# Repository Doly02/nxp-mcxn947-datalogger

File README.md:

## Digital Data Logger with Information Loss Prevention in Case of Power Failure

- Author: Tomáš Dolák 
- Login: [xdolak09](https://www.vut.cz/lide/tomas-dolak-247220)
- Email: <xdolak09@stud.fit.vutbr.cz>
- Supervisor: Ing. Václav Šímek
- Consultant: Ing. Martin Moštěk PhD. (NXP Semiconductors)

The goal of this project is to develop a digital data logger that captures serial data from a UART peripheral, timestamps it, and stores the logged data on an SD card.
A key requirement of the implementation is to ensure data integrity by preventing loss in the event of a power failure. This digital data logger was developed based on the requirements provided by the Wireless Charging Team at NXP Semiconductors.

### Table of Contents
- [Requirements](#requirements)
  - [Hardware Components](#hardware-components)
  - [Software Requirements](#software-requirements)
- [Repository Organization](#repository-organization)
- [How to Use the Digital Data Logger](#how-to-use-the-digital-data-logger)
  - [USB Interfaces](#usb-interfaces)
  - [Signal Diodes](#signal-diodes)
  - [Data Recording](#data-recording)
  - [Reading Data from the Data Logger](#reading-data-from-the-data-logger)
  - [Structure of Logged Data](#structure-of-logged-data)
  - [Format of Logged Entries](#format-of-logged-entries)
- [Developer Notes](#developer-notes)
  - [Modules](#modules)
- [Testing](#testing)
  - [Functional Testing](#functional-testing)
  - [Static Code Analysis](#static-code-analysis)
- [Documentation](#documentation)
- [Known Issues](#known-issues)
- [References](#references)

### Requirements 
To build and run `datalogger`, you will need the following:

#### Hardware Components
1. NXP FRDM-MCXN947 Development Board
2. Expansion Shield Proposed in This Bachelor Thesis

#### Software Requirements
1. MCUXpresso IDE v11.10.0 With GCC-based ARM Embedded Toolchain (Arm-none-eabi-gcc Compiler)
1. NXP SDK FRDM-MCXN947 Version 2.16.000

### Repository Organization
```
/nxp-mcxn947-datalogger
├── application/                 # Main Directory With Digital Recorder Firmware.
│   ├── src/                  # Contains The Firmware Source Files.
│   ├── doc/                     # HTML and LaTeX Firmware Documentation Generated by Doxygen.
│   ├── include/                 # Contains The Firmware Header Files.
│   └── others...                # Project Files (.cproject & .project), Libraries (e.g. FATFS), FreeRTOS, Utilities, Modules and Drivers From NXP SDK.
│
├── hardware/
│   ├── components/              # List of Used Hardware Components on Expansion Shield.
│   ├── design/                  # KiCAD Project Containing Schematic and PCB Design.
│   └── pinout_datalogger.xlsx   # Table With Overview of Microcontroller Pin Connections.
├── power_consumption/           # Digital Data Logger Power Consumption Data, Measured By Power Profiler Kit II. [1]
├── tests/
│   ├── functional_tests/        # Functional Test Folder For Verifying Correct Data Collection.
│   │   ├── test_files/          # Test Files Used By serial_tests.py Script.
│   │   ├── stress_test.py       # Script With Stress Test For Digital Data Logger Sends Data Continiously With Baudrate 921600.
│   │   └── serial_tests.py      # serial_tests.py Script.
│   └── static_analysis/
│       ├── outputs/             # Contains Outputs of Static Code Analysis According To MISRA C:2012 Rules, Performed by PC-lint Tool.
│       ├── parsers/             # Contains Parsers That Filter Rule-Breakings MISRA Rules From The Required and Mandatory Categories.
│       ├── lint_config.lnt      # Configuration File of PC Lint Plus.
│       └── sources.lst          # Defines a Set of Files To Be Analyzed by PC Lint Plus.
│
├── thesis/                                     # Sub-Module
│   ├── xdolak09-bthesis.tex                    # Main LaTeX Project of Technical Report.
│   ├── project-01-kapitoly-chapters.tex        # Chapters LaTeX Project of Technical Report.
│   ├── project-20-literatura-bibliography.bib  # Bibliography of Technical Report.
│   ├── project-30-prilohy-appendices.tex       # Appendices of Technical Report.
│   ├── table-of-extraneous-words.tex           # Table of Extraneous Words in Technical Report.
│   ├── bib-styles
│   ├── obrazky-figures/         # Used Figures.
│   ├── template-fig/            # VUT Logo.
│   └── diagrams/                # Created Digrams For Technical Report.
│
├── config                       # Contains a Sample Configuration File That Can Be Used To Configure The Behaviour of The Digital Recorder.
├── README.md
```

### How to Use the Digital Data Logger

#### Signal Diodes

The digital data logger is equipped with five status LEDs (labeled 1–5) located on the front side of the enclosure. These LEDs visually indicate the current operational state of the logger.

The image below shows the placement and labeling of each LED on the front panel of the enclosure:

<p align="center">
  <br>
  <em>Data logger status LEDs </em><br>
</p>

The table below describes the function of each LED:

| LED | Description |
|-----|-------------|
| 1   | Lights up when the available free space on the SD card falls below the limit defined by the `free_space` parameter in the configuration file. |
| 2   | Indicates an error condition. This LED turns on if the configuration file is invalid or if a critical error occurs during data recording (e.g., file creation failure or UART framing error). |
| 3   | Signals that the data logger is no longer actively recording. This state occurs, for example, when the monitored device stops transmitting data or is disconnected. |
| 4   | Blinks during active data recording to indicate that data is being received and saved to the SD card. |
| 5   | Lights up approximately 16 seconds after powering the logger to indicate that the backup capacitor is sufficiently charged. Once lit, it is safe to disconnect the device from power without risking data loss. |

#### Data Recording
1. **(Optional But Recommended)** Prepare the configuration file `config`, which should be placed in the root directory of the SD card.  
This file allows you to customize the data logger's behavior instead of using the default configuration.

<p align="center">
  <br>
  <em>Location of the config file on the SD card</em><br>
</p>

Example content of `config`:
```
baudrate=115200
file_size=2048
stop_bits=1
data_bits=8
parity=none
free_space=50
```
- **Note:** The order of parameters is not fixed.

If some of the parameters in the configuration file are missing or the configuration file is missing completely,  
the default values defined in the `defs.h` file are used.

| Parameter      | Default Value                 | Data Type                      |
|----------------|-------------------------------|--------------------------------|
| `baudrate`     | `230400`                      | uint32_t                       |
| `file_size`    | `8192`                        | uint32_t (in KiB)              |
| `stop_bits`    | `kLPUART_OneStopBit`          | enum (lpuart_stop_bit_count_t) |
| `data_bits`    | `kLPUART_EightDataBits`       | enum (lpuart_data_bits_t)      |
| `parity`       | `kLPUART_ParityDisabled`      | enum (lpuart_parity_mode_t)    |
| `free_space`   | `50`                          | uint32_t (in MiB)              |

2. Insert the SD card (type SDHC) into the data logger.

3. Power on the data logger via USB or another power source. The data logger will automatically:
- Load the configuration from `config` (if present)
- After startup, the data logger enters the recording mode by default. At the beginning of the record task, it initializes the SD card, and if a new or unformatted card is detected,  
  the firmware will automatically format it and initialize the FAT file system with 32-bit LBA.

4. Wait until the LED 5 indicator turns on.  
   This LED indicates that the digital data logger can be safely disconnected without the risk of data loss or file system corruption.

5. Connect the digital data logger to the monitored device that transmits serial data via UART.  
   Once the data transmission starts, the data logger will indicate active reception by blinking a dedicated LED 4,  
   which is shown in the following image.

6. At this point, the digital data logger is actively recording incoming UART data.  
   During recording, the same LED continuously blinks to indicate that data logging is in progress.

7. If an error occurs during UART data reception (e.g. framing error),  
   the digital data logger will illuminate a separate error LED 2  
   to indicate that logging has been interrupted due to a fault.

   If the error prevents further data reception, an additional LED 3 will also light up  
   to signal that the device can no longer continue logging until it is restarted or the error is resolved.

8. To safely stop data logging, disconnect the digital data logger from the monitored device.  
   At this point, all buffered data will be properly finalized and stored on the SD card.  
   The status LED D3 will then light up to indicate that data reception has been halted  
   and the device is in standby mode.

9. To resume data logging after it has been halted, simply reconnect the digital data logger  
   to the monitored UART device. The logger will automatically return to recording mode  
   (described in step 6) and continue capturing incoming data.

10. In the event of a power disconnection during logging,  
    the digital data logger detects the power loss and automatically saves all buffered data.  
    The recording is then gracefully finalized to prevent data loss or file system corruption.

#### Reading Data from the Data Logger
To read the recorded data from the digital data logger, simply connect the device to a computer using the USB1_HS connector.  
The data logger will automatically switch into data access mode (MSC mode), and the SD card will be exposed as a standard mass storage device,  
allowing the user to copy the recorded data files.

<p align="center">
  <br>
  <em>Organization of session directories with logs on SD cards</em><br>
</p>

#### Structure of Logged Data
After each startup, the data logger creates a new session directory in which all the logs from the current runtime are stored.  
These session folders are organized by the date and an incrementing counter in the format:

```
YYYYMMDD_X/
```

Where:  
- `YYYYMMDD` is the date of the session creation  
- `X` is an integer session index used to differentiate multiple sessions created on the same day

After data has been recorded, each session folder contains text-based log files storing the data collected during the corresponding session.  
The maximum size of each log file is determined by the `file_size` parameter defined in the configuration file (see chapter on configuration).  
Log files are named using the following format:

```
YYYYMMDD_HHMMSS_X.txt
```

- `YYYYMMDD_HHMMSS` is the timestamp when the log file was created  
- `X` is an index used to differentiate multiple files created at the same second

#### Format of Logged Entries
Each logged line represents a single data record terminated by a line break sequence (`\r\n`).  
Every line is prefixed with a timestamp in the format:

```
(HH:MM:SS) Logged Message
```

This timestamp represents the time when the specific data was captured by the logger.  
The following example illustrates the typical appearance of consecutive logged lines in a file:

```
(00:10:16) New Data 23741
(00:10:16) New Data 23742
(00:10:16) New Data 23743
(00:10:16) New Data 23744
(00:10:16) New Data 23745
(00:10:16) New Data 23746
(00:10:16) New Data 23747
(00:10:16) New Data 23748
(00:10:16) New Data 23749
```

### Developer Notes
All application-level source and header files are located in the `source/` and `include/` directories.

The firmware is structured into several functional modules, such as recording logic, mass storage access, power loss detection, and system status signaling.  
Many of these modules can be individually enabled or disabled as needed. This behavior is achieved through conditional compilation in ISO C, and logic blocks are active only  
if enabled via preprocessor macros. These settings are centrally managed in the application configuration header file `defs.h`.

The `defs.h` configuration file also includes the option to control the verbosity of firmware output messages. The firmware supports three message output levels:

- **Error Messages** (prefixed with `ERR:`) report critical conditions. This level is always active and can't be disabled.

```
PRINTF("ERR: Failed to Create File %s. Error=%d\r\n", u8FileName, (uint32_t)status);
```

- **Informational Messages** (prefixed with `INFO:`) provide context such as initialization progress, configuration file loading, creation of log, etc.

```
PRINTF("INFO: Created Log %s.\r\n", u8FileName);
```

- **Debug messages** (prefixed with `DEBUG:`) offer the most detailed output and include additional technical details useful during development.

```
PRINTF("DEBUG: File System Not Found. Creating FAT File System...\r\n");
```

All of these outputs are provided through the UART serial interface. The firmware uses the `LP_FLEXCOMM4` UART peripheral instance,  
configured with the following parameters:

| Parameter      | Value    | 
|----------------|----------|
| Baudrate       | 115200   |
| Data Bits      | 8        |
| Stop Bit       | 1        |
| Parity         | None     |

The firmware runs on the FreeRTOS real-time operating system. To ensure maximum reliability and predictability, only static memory  
allocation is used throughout the firmware. All tasks and synchronization primitives are created with predefined memory sizes,  
and dynamic memory allocation is fully disabled in the FreeRTOS configuration. Additionally, specific memory allocation functions  
for system tasks such as the idle task and timer task have been implemented to support fully static operation.

The overall hardware and software initialization procedures are handled by the `APP_InitBoard()` function, declared in the header file _app_initialization.h_  
and defined in the source file _app_initialization.c_.

The application consists of two FreeRTOS tasks – _record_task_, which is responsible for recording UART data, and _msc_task_, responsible for exposing the recorded data  
via USB. These tasks are implemented in `app_tasks.c` and `pp_tasks.h`, and are created and started from within the `main.c` file.

### Modules
The application files (`main.c`, `app_tasks.c`, and `app_initialization.c`) utilize the following separate modules.  
Each module has its own source and header file:

- `error` – Handles errors and defines error codes.  
- `led` – Manages LED Indicators For System Status.
- `mass_storage` – Provides access to log files over USB MSC.  
- `parser` – Parses the configuration file (`config`) from the SD card.
- `pwrloss_det` – Detects and reacts to power loss.
- `record` – Implements logic for recording incoming serial data from UART.
- `task_switching` – Includes the method for detection of attached or detached application USB.
- `time` – Provides date/time handling for file naming and timestamping (external and internal RTCs).
- `uart` – Includes initialization (+ configuration), enabling and disabling of the UART peripheral.  
- `temperature` – Extension for temperature measurement using the P3T1755 on-board temperature sensor on the FRDM-MCXN947.

### Testing

#### Functional Testing
The digital data logger was tested using a Python script located in the `tests/` directory under the name `serial_test.py`.

The script `serial_test.py` simulates the monitored device by reading test text files and sending their contents as serial data through the COM port to the digital data logger.  
There is a time delay between each file being sent, which deliberately causes the `CONSOLELOG_Flush()` function to be called,  
so that each test input is recorded in a separate file that can be compared against the original test file.

Scripted testing was performed at various baud rates, with testing primarily focused on baud rates corresponding to actual deployment scenarios.  
After the test was completed, the recorded outputs were compared to the original test files. The results of the comparison confirmed that in all cases tested,  
the transfer was correct and there was no data loss or corruption.

The digital data logger was also successfully verified using the `stress_test.py` script that contains a stress test.  
In this test, data was sent at 921600 baud. The data was first collected into a circular buffer of 4 KiB,  
from which it was then stored on the SD card in blocks of 4 KiB. The resulting recording files were 1 MiB in size.

Functional testing also covered the behavior of the digital recorder in non-standard scenarios that may occur during real-world deployment.The Results are Summarized in Table Below.

| Test description                                                      | Expected result                                                                                   | Passed |
|-----------------------------------------------------------------------|---------------------------------------------------------------------------------------------------|--------|
| Missing configuration file                                            | Error indication using LED D2, recording interrupted                                              | Yes    |
| Missing `baudrate` value in configuration                             | Start recording with default `baudrate` value                                                     | Yes    |
| Recording on a new unformatted SD card                                | SD card is formatted, file system initialized, and device then records incoming data              | Yes    |
| Recording with file size of 512 B                                     | File created and properly closed upon reaching limit                                              | Yes    |
| Recording with file size of 1 MB                                      | File created and properly closed upon reaching limit                                              | Yes    |
| Low free SD card capacity (i.e., below value of parameter `free_space`) | Indication via LED                                                                                | Yes    |
| Transfer of recorded data from the digital recorder                   | Records transferred to host device from the digital recorder                                      | Yes    |

#### Static Code Analysis
In addition to functional testing, static analysis of the source code was performed using rules from the MISRA (_Motor Industry Software Reliability Association_) specification, specifically MISRA C:2012. The focus was primarily on rules classified as required and mandatory. All detected violations in these categories were either corrected or justified through comments in the source code, including a reference to the relevant rule and a rationale for the exception.

The code analysis was performed with tool PC-lint Plus v2.2 developed by Vector. [2]

#### Documentation

This project provides a full range of documentation.

- The hardware and software design concepts are described in detail in the technical report, which is available in folder `thesis/` under name `xdolak09-bthesis.pdf`
- The firmware documentation is located in the `application/doc/` directory. It is generated using Doxygen and available in two formats:
  1. **HTML documentation** - open the file `annotated.html` on the path `application/doc/html/`to start browsing.
  2. **LaTeX documentation** - found under `application/doc/latex` , where the main output file is `refman.pdf`.

### Known Issues
No issues were observed during development, testing, or practical usage of the digital data logger.

### References
[1] "Nordic Semiconductors Power Profiler Kit II" [online]. [cited 2025-5-6]. Available at [https://www.nordicsemi.com/Products/Development-hardware/Power-Profiler-Kit-2](https://www.nordicsemi.com/Products/Development-hardware/Power-Profiler-Kit-2)

[2] "PC-lint Plus 2.2 Static Code Analysis Tool for C and C++ Source Code" [online]. [cited 2025-5-6]. Available at [https://pclintplus.com/](https://pclintplus.com/)

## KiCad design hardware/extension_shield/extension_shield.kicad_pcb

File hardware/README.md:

# Hardware Documentation

This folder contains all hardware-related materials for the expansion shield designed for the FRDM-MCXN947 development board used in data logger project.

### Folder Structure

- `expansion_shield/` – Contains the full KiCad 8 project of the expansion board. This includes the schematic, PCB layout, and associated design files.
- `BOM.csv` – A standard bill of materials generated from KiCad 8 listing the components used on the expansion board.  
- `component.txt` – A human-readable version of the BOM, listing key components along with direct links to online distributors for easy purchasing.  
  **Note:** This list does **not** include passive components such as resistors and capacitor (100 nF) used for the RTC DS3231M+.
- `schematic.pdf` – A PDF version of the complete schematic diagram of the expansion shield for quick reference without needing KiCad.

### Notes
- The KiCad project is created with **KiCad 8**. Make sure to use the correct version to avoid compatibility issues.
- The provided component links in `component.txt` were valid at the time of writing but may change over time depending on distributor availability.

For more information about the system design, refer to the `thesis/` folder or see the main `README` in root folder.

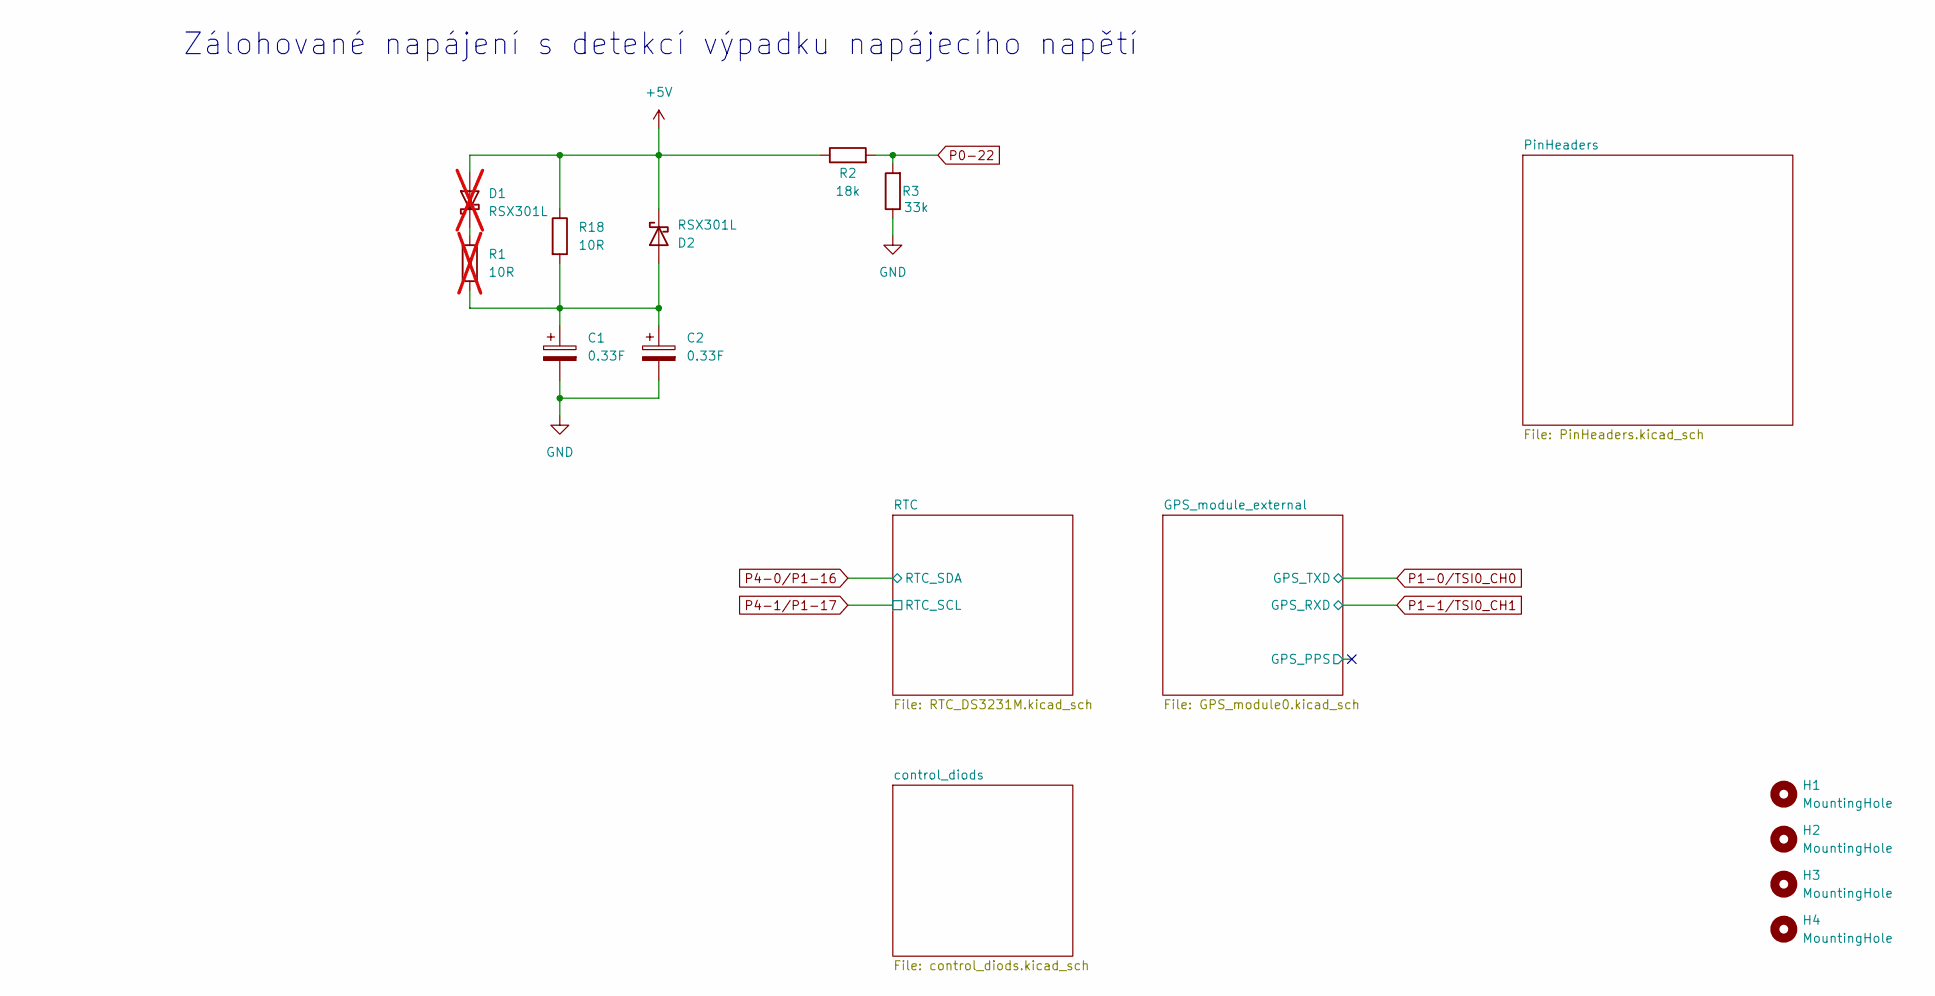
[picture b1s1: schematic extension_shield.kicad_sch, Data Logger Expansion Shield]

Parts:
C1, C2: 0.33F; C_Radial_D8mm_W24mm_L14mm_P13.5mm
D1: RSX301L; D_SMA; not fitted
D2: RSX301L; D_SMA
H1, H2, H3, H4: MountingHole; MountingHole_3.2mm_M3
R1: 10R; R_Axial_DIN0204_L3.6mm_D1.6mm_P5.08mm_Horizontal; not fitted
R2: 18k; R_1206_3216Metric_Pad1.30x1.75mm_HandSolder
R3: 33k; R_1206_3216Metric_Pad1.30x1.75mm_HandSolder
R18: 10R; R_Axial_DIN0204_L3.6mm_D1.6mm_P5.08mm_Horizontal

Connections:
+5V: D1.2 (A), D2.1 (K), R2.1, R18.1; also elsewhere on the board
GND: C1.2, C2.2, R3.1; also elsewhere on the board
unnamed: D1.1 (K), R1.1
unnamed: C1.1, C2.1, D2.2 (A), R1.2, R18.2
P0-22: R2.2, R3.2; also elsewhere on the board

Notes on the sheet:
Zálohované napájení s detekcí výpadku napájecího napětí

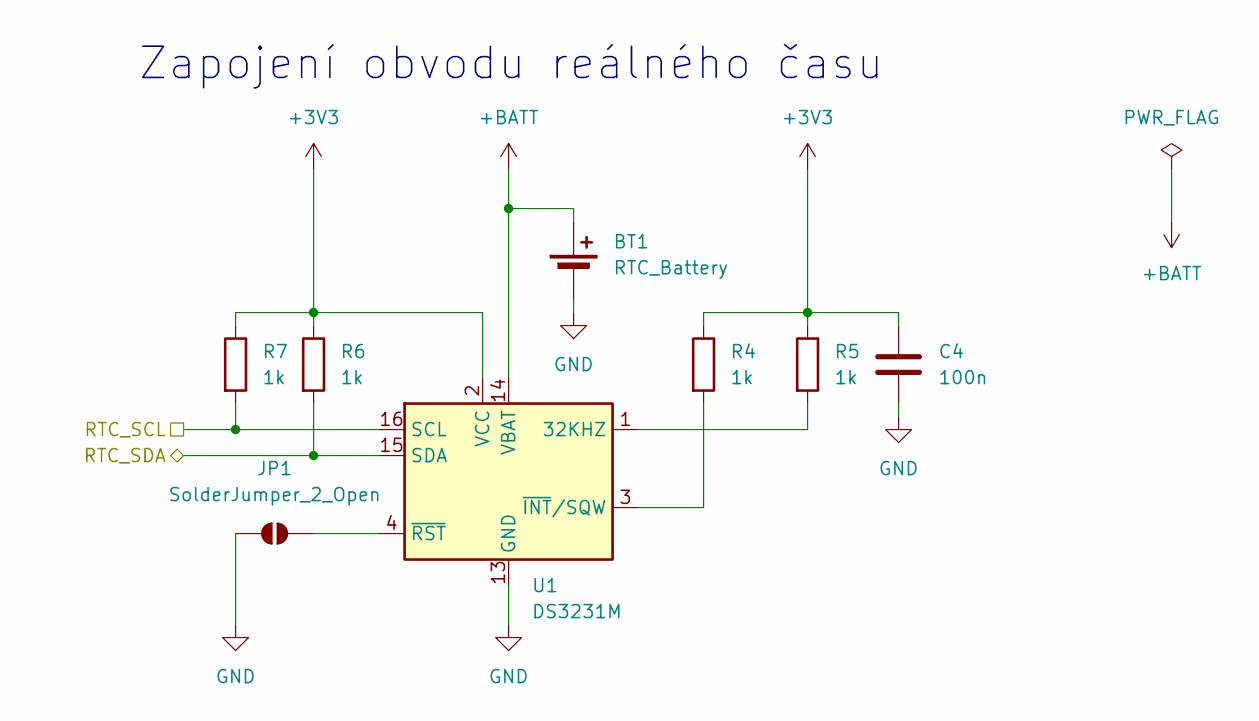
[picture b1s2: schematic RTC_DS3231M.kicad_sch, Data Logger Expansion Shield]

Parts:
BT1: RTC_Battery; Battery_Panasonic_CR2032-HFN_Horizontal_CircularHoles
C4: 100n; C_1206_3216Metric_Pad1.33x1.80mm_HandSolder
JP1: SolderJumper_2_Open; SolderJumper-2_P1.3mm_Open_Pad1.0x1.5mm
R4, R5, R6, R7: 1k; R_1206_3216Metric_Pad1.30x1.75mm_HandSolder
U1: DS3231M; SOIC-16W_7.5x10.3mm_P1.27mm

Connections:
+3V3: C4.1, R4.1, R5.1, R6.1, R7.1, U1.2 (VCC); also elsewhere on the board
+BATT: BT1.1 (+), U1.14 (VBAT)
GND: BT1.2 (-), C4.2, JP1.1 (A), U1.5 (GND), U1.6 (GND), U1.7 (GND), U1.8 (GND), U1.9 (GND), U1.10 (GND), U1.11 (GND), U1.12 (GND), U1.13 (GND); also elsewhere on the board
unnamed: JP1.2 (B), U1.4 (~RST)
unnamed: R5.2, U1.1 (32KHZ)
unnamed: R4.2, U1.3 (~INT/SQW)
P4-0/P1-16: R6.2, U1.15 (SDA); also elsewhere on the board
P4-1/P1-17: R7.2, U1.16 (SCL); also elsewhere on the board

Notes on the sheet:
Zapojení obvodu reálného času

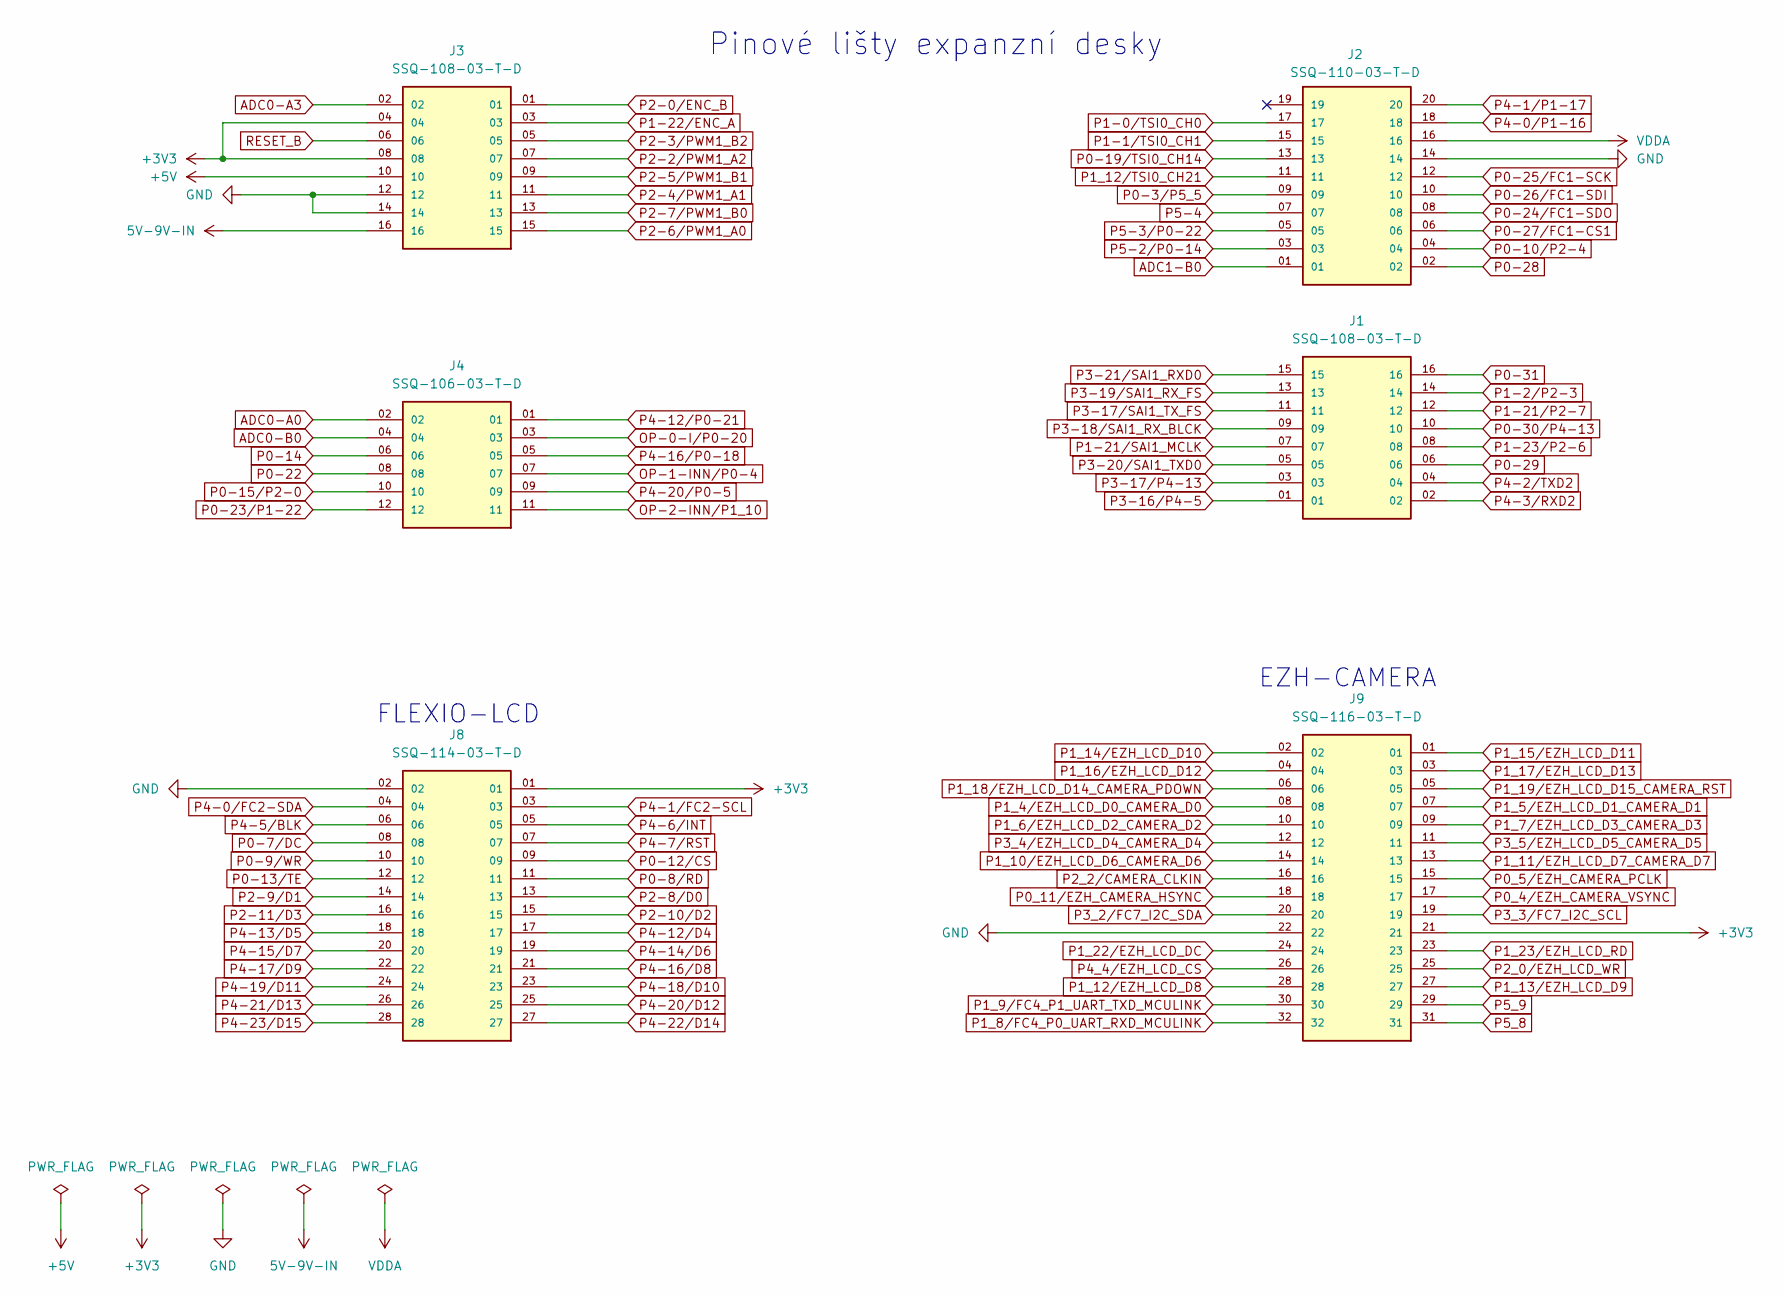
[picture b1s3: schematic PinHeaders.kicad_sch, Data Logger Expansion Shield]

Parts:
J1, J3: SSQ-108-03-T-D; SAMTEC_SSQ-108-XX-X-D; PARTREV A
J2: SSQ-110-03-T-D; SAMTEC_SSQ-110-03-T-D; PARTREV R
J4: SSQ-106-03-T-D; SAMTEC_SSQ-106-03-T-D; PARTREV R
J8: SSQ-114-03-T-D; SAMTEC_SSQ-114-03-T-D; PARTREV R
J9: SSQ-116-03-T-D; SAMTEC_SSQ-116-XX-X-D; PARTREV A

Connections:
5V-9V-IN: J3.16
+3V3: J3.04, J3.08, J8.01, J9.21; also elsewhere on the board
+5V: J3.10; also elsewhere on the board
ADC0-A0: J4.02
ADC0-A3: J3.02
ADC0-B0: J4.04
ADC1-B0: J2.01
GND: J2.14, J3.12, J3.14, J8.02, J9.22; also elsewhere on the board
OP-0-I/P0-20: J4.03
OP-1-INN/P0-4: J4.07
OP-2-INN/P1_10: J4.11
P0-3/P5_5: J2.09
P0-7/DC: J8.08; also elsewhere on the board
P0-8/RD: J8.11
P0-9/WR: J8.10; also elsewhere on the board
P0-10/P2-4: J2.04
P0-12/CS: J8.09
P0-13/TE: J8.12; also elsewhere on the board
P0-14: J4.06
P0-15/P2-0: J4.10
P0-19/TSI0_CH14: J2.13
P0-22: J4.08; also elsewhere on the board
P0-23/P1-22: J4.12
P0-24/FC1-SDO: J2.08
P0-25/FC1-SCK: J2.12
P0-26/FC1-SDI: J2.10
P0-27/FC1-CS1: J2.06
P0-28: J2.02
P0-29: J1.06
P0-30/P4-13: J1.10
P0-31: J1.16
P0_4/EZH_CAMERA_VSYNC: J9.17
P0_5/EZH_CAMERA_PCLK: J9.15
P0_11/EZH_CAMERA_HSYNC: J9.18
P1-0/TSI0_CH0: J2.17; also elsewhere on the board
P1-1/TSI0_CH1: J2.15; also elsewhere on the board
P1-2/P2-3: J1.14
P1-21/P2-7: J1.12
P1-21/SAI1_MCLK: J1.07
P1-22/ENC_A: J3.03
P1-23/P2-6: J1.08
P1_4/EZH_LCD_D0_CAMERA_D0: J9.08
P1_5/EZH_LCD_D1_CAMERA_D1: J9.07
P1_6/EZH_LCD_D2_CAMERA_D2: J9.10
P1_7/EZH_LCD_D3_CAMERA_D3: J9.09
P1_8/FC4_P0_UART_RXD_MCULINK: J9.32
P1_9/FC4_P1_UART_TXD_MCULINK: J9.30
P1_10/EZH_LCD_D6_CAMERA_D6: J9.14
P1_11/EZH_LCD_D7_CAMERA_D7: J9.13
P1_12/EZH_LCD_D8: J9.28
P1_12/TSI0_CH21: J2.11
P1_13/EZH_LCD_D9: J9.27
P1_14/EZH_LCD_D10: J9.02
P1_15/EZH_LCD_D11: J9.01
P1_16/EZH_LCD_D12: J9.04
P1_17/EZH_LCD_D13: J9.03
P1_18/EZH_LCD_D14_CAMERA_PDOWN: J9.06
P1_19/EZH_LCD_D15_CAMERA_RST: J9.05
P1_22/EZH_LCD_DC: J9.24
P1_23/EZH_LCD_RD: J9.23
P2-0/ENC_B: J3.01
P2-2/PWM1_A2: J3.07
P2-3/PWM1_B2: J3.05
P2-4/PWM1_A1: J3.11
P2-5/PWM1_B1: J3.09
P2-6/PWM1_A0: J3.15
P2-7/PWM1_B0: J3.13
P2-8/D0: J8.13
P2-9/D1: J8.14
P2-10/D2: J8.15
P2-11/D3: J8.16; also elsewhere on the board
P2_0/EZH_LCD_WR: J9.25
P2_2/CAMERA_CLKIN: J9.16
P3-16/P4-5: J1.01
P3-17/P4-13: J1.03
P3-17/SAI1_TX_FS: J1.11
P3-18/SAI1_RX_BLCK: J1.09
P3-19/SAI1_RX_FS: J1.13
P3-20/SAI1_TXD0: J1.05
P3-21/SAI1_RXD0: J1.15
P3_2/FC7_I2C_SDA: J9.20
P3_3/FC7_I2C_SCL: J9.19
P3_4/EZH_LCD_D4_CAMERA_D4: J9.12
P3_5/EZH_LCD_D5_CAMERA_D5: J9.11
P4-0/FC2-SDA: J8.04
P4-0/P1-16: J2.18; also elsewhere on the board
P4-1/FC2-SCL: J8.03
P4-1/P1-17: J2.20; also elsewhere on the board
P4-2/TXD2: J1.04
P4-3/RXD2: J1.02
P4-5/BLK: J8.06
P4-6/INT: J8.05
P4-7/RST: J8.07
P4-12/D4: J8.17
P4-12/P0-21: J4.01
P4-13/D5: J8.18
P4-14/D6: J8.19
P4-15/D7: J8.20
P4-16/D8: J8.21
P4-16/P0-18: J4.05
P4-17/D9: J8.22; also elsewhere on the board
P4-18/D10: J8.23
P4-19/D11: J8.24
P4-20/D12: J8.25
P4-20/P0-5: J4.09
P4-21/D13: J8.26
P4-22/D14: J8.27
P4-23/D15: J8.28
P4_4/EZH_LCD_CS: J9.26
P5-2/P0-14: J2.03
P5-3/P0-22: J2.05
P5-4: J2.07
P5_8: J9.31
P5_9: J9.29
RESET_B: J3.06
VDDA: J2.16

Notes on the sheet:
FLEXIO-LCD
Pinové lišty expanzní desky
EZH-CAMERA

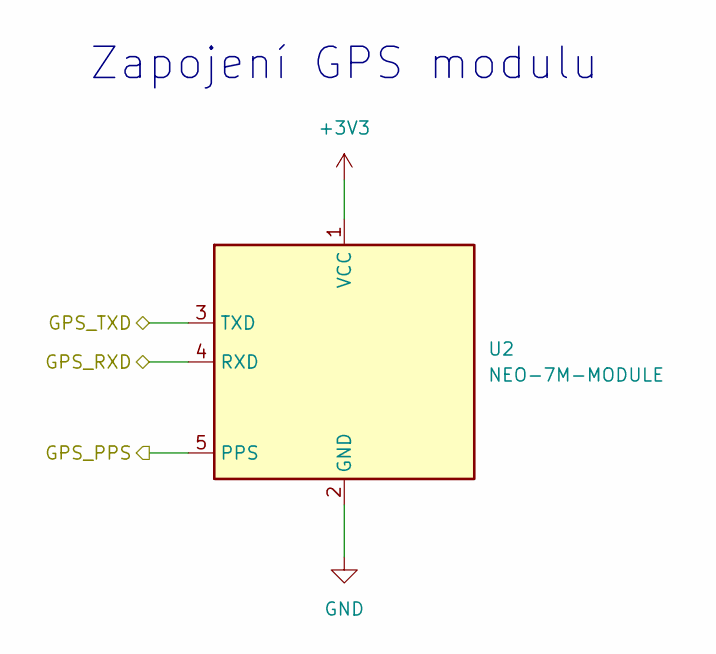
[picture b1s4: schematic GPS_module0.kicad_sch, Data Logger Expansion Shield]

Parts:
U2: NEO-7M-MODULE; Neo-7M-Module

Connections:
+3V3: U2.1 (VCC); also elsewhere on the board
/GPS_module_external/GPS_PPS: U2.5 (PPS)
GND: U2.2 (GND); also elsewhere on the board
P1-0/TSI0_CH0: U2.3 (TXD); also elsewhere on the board
P1-1/TSI0_CH1: U2.4 (RXD); also elsewhere on the board

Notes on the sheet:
Zapojení GPS modulu

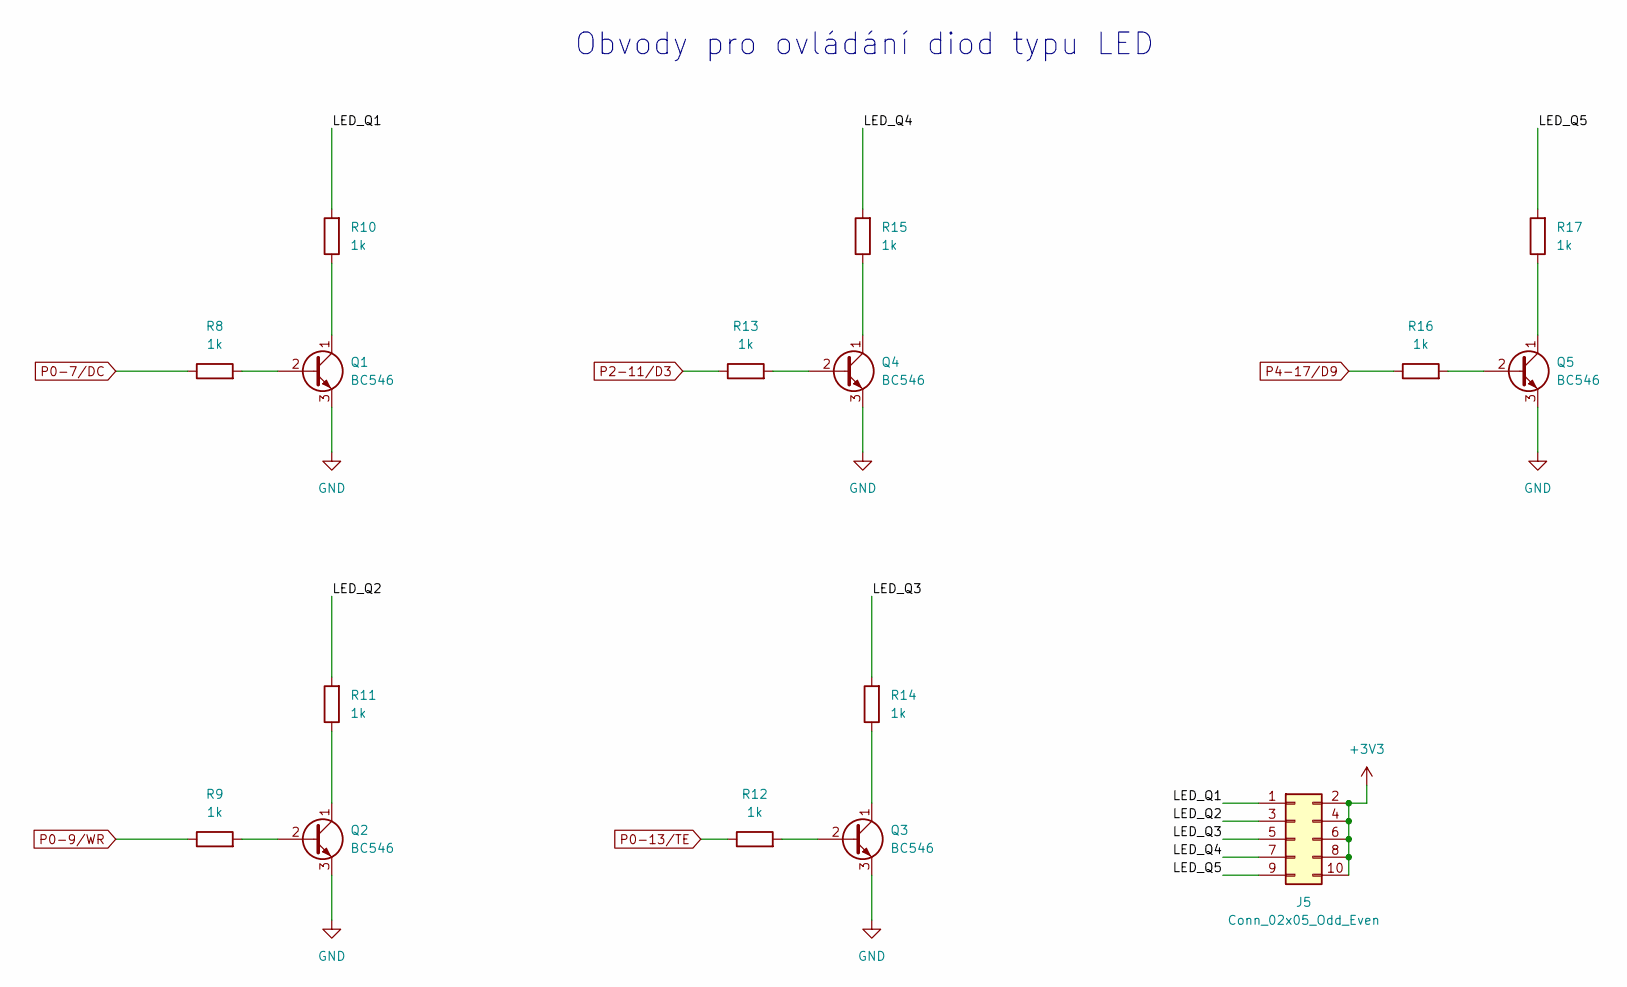
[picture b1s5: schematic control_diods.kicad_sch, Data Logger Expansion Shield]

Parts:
J5: Conn_02x05_Odd_Even; PinSocket_2x05_P2.54mm_Vertical
Q1, Q2, Q3, Q4, Q5: BC546; TO-92_Inline
R8, R9, R10, R11, R12, R13, R14, R15, R16, R17: 1k; R_1206_3216Metric_Pad1.30x1.75mm_HandSolder

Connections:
+3V3: J5.2, J5.4, J5.6, J5.8, J5.10; also elsewhere on the board
/control_diods/LED_Q1: J5.1, R10.2
/control_diods/LED_Q2: J5.3, R11.2
/control_diods/LED_Q3: J5.5, R14.2
/control_diods/LED_Q4: J5.7, R15.2
/control_diods/LED_Q5: J5.9, R17.2
GND: Q1.3 (E), Q2.3 (E), Q3.3 (E), Q4.3 (E), Q5.3 (E); also elsewhere on the board
unnamed: Q1.2 (B), R8.2
unnamed: Q1.1 (C), R10.1
unnamed: Q2.2 (B), R9.2
unnamed: Q2.1 (C), R11.1
unnamed: Q3.2 (B), R12.2
unnamed: Q3.1 (C), R14.1
unnamed: Q4.2 (B), R13.2
unnamed: Q4.1 (C), R15.1
unnamed: Q5.2 (B), R16.2
unnamed: Q5.1 (C), R17.1
P0-7/DC: R8.1; also elsewhere on the board
P0-9/WR: R9.1; also elsewhere on the board
P0-13/TE: R12.1; also elsewhere on the board
P2-11/D3: R13.1; also elsewhere on the board
P4-17/D9: R16.1; also elsewhere on the board

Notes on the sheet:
Obvody pro ovládání diod typu LED

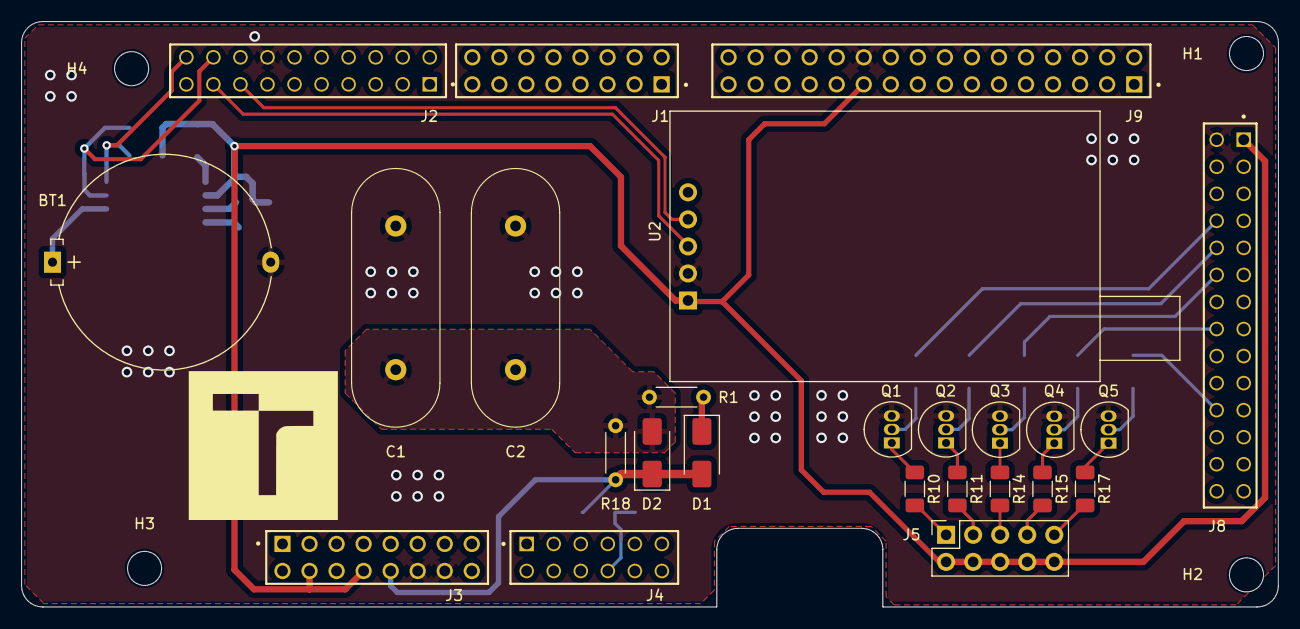
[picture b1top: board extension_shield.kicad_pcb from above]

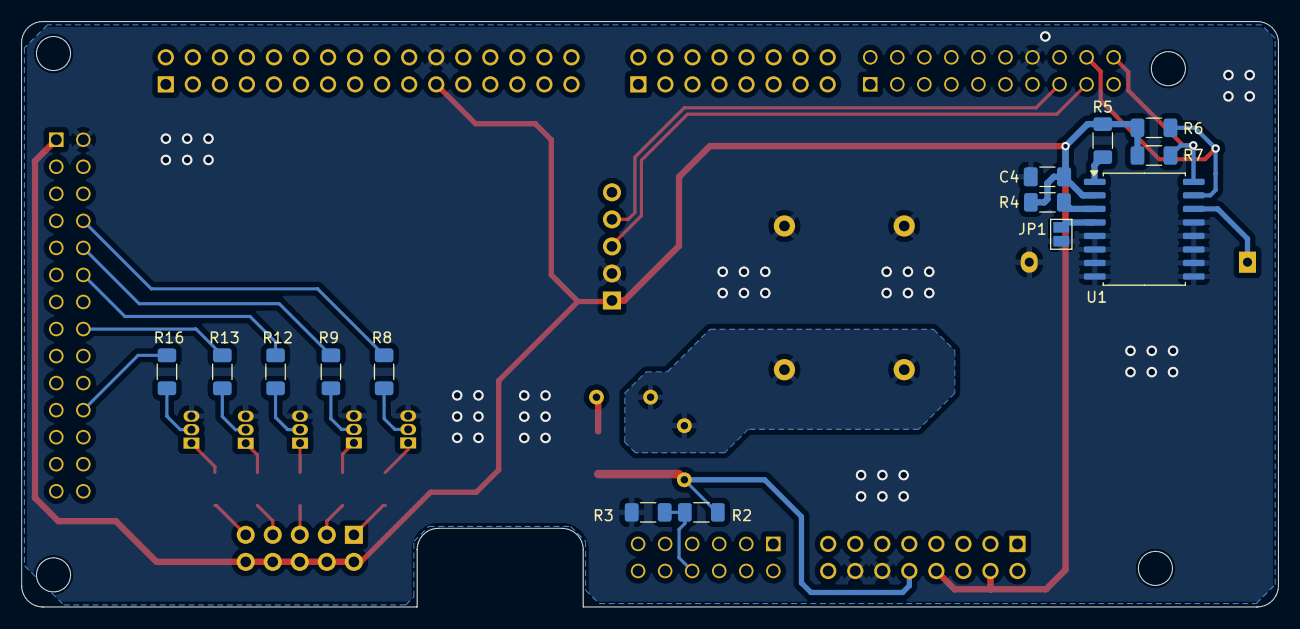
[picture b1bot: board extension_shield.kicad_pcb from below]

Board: 2 copper layers, 118.1 x 55.0 mm, 43 parts (14 on the bottom side), 34 nets.

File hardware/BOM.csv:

"Reference","Value","Datasheet","Footprint","Qty","DNP"
"BT1","RTC_Battery","~","Battery:Battery_Panasonic_CR2032-HFN_Horizontal_CircularHoles","1",""
"C1,C2","0.33F","https://cz.mouser.com/ProductDetail/581-SCMT32H755SRBB0","SuperCapacitors:C_Radial_D8mm_W24mm_L14mm_P13.5mm","2",""
"C4","100n","~","Capacitor_SMD:C_1206_3216Metric_Pad1.33x1.80mm_HandSolder","1",""
"D1","RSX301L","https://fscdn.rohm.com/en/products/databook/datasheet/discre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","Diode_SMD:D_SMA","1","DNP"
"D2","RSX301L","https://fscdn.rohm.com/en/products/databook/datasheet/discre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","Diode_SMD:D_SMA","1",""
"J1,J3","SSQ-108-03-T-D","https://suddendocs.samtec.com/catalog_english/ssq_th.pdf","SSQ-xxx-03-T-D:SAMTEC_SSQ-108-XX-X-D","2",""
"J2","SSQ-110-03-T-D","https://suddendocs.samtec.com/catalog_english/ssq_th.pdf","SSQ-xxx-03-T-D:SAMTEC_SSQ-110-03-T-D","1",""
"J4","SSQ-106-03-T-D","https://suddendocs.samtec.com/catalog_english/ssq_th.pdf","SSQ-xxx-03-T-D:SAMTEC_SSQ-106-03-T-D","1",""
"J5","Conn_02x05_Odd_Even","https://cz.mouser.com/datasheet/2/181/M20-783-1133465.pdf","Connector_PinSocket_2.54mm:PinSocket_2x05_P2.54mm_Vertical","1",""
"J8","SSQ-114-03-T-D","https://suddendocs.samtec.com/catalog_english/ssq_th.pdf","SSQ-xxx-03-T-D:SAMTEC_SSQ-114-03-T-D","1",""
"J9","SSQ-116-03-T-D","https://suddendocs.samtec.com/catalog_english/ssq_th.pdf","SSQ-xxx-03-T-D:SAMTEC_SSQ-116-XX-X-D","1",""
"Q1,Q2,Q3,Q4,Q5","BC546","https://www.onsemi.com/pub/Collateral/BC550-D.pdf","Package_TO_SOT_THT:TO-92_Inline","5",""
"R1","10R","~","Resistor_THT:R_Axial_DIN0204_L3.6mm_D1.6mm_P5.08mm_Horizontal","1","DNP"
"R2","18k","~","Resistor_SMD:R_1206_3216Metric_Pad1.30x1.75mm_HandSolder","1",""
"R3","33k","~","Resistor_SMD:R_1206_3216Metric_Pad1.30x1.75mm_HandSolder","1",""
"R4,R5,R6,R7,R8,R9,R10,R11,R12,R13,R14,R15,R16,R17","1k","~","Resistor_SMD:R_1206_3216Metric_Pad1.30x1.75mm_HandSolder","14",""
"R18","10R","~","Resistor_THT:R_Axial_DIN0204_L3.6mm_D1.6mm_P5.08mm_Horizontal","1",""
"U1","DS3231M","http://datasheets.maximintegrated.com/en/ds/DS3231.pdf","Package_SO:SOIC-16W_7.5x10.3mm_P1.27mm","1",""
"U2","NEO-7M-MODULE","https://www.mouser.co.uk/datasheet/2/1025/NEO_7_DataSheet__U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","Neo7M_Module_Lib:Neo-7M-Module","1",""
